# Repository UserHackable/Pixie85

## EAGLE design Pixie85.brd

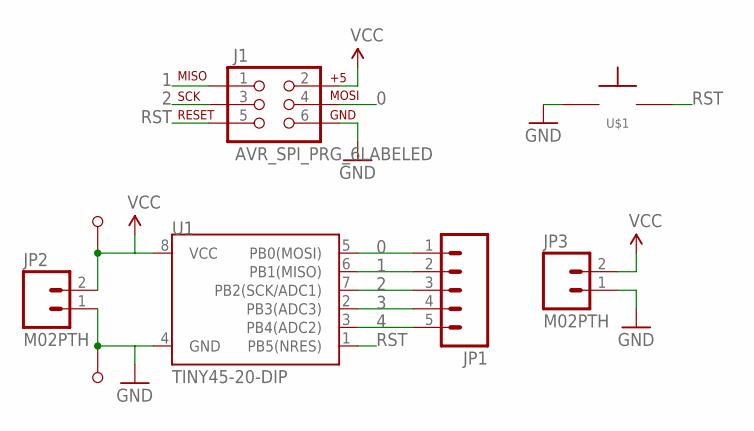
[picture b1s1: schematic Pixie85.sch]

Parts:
+: M1; M1_NO_STRAIN
-: M1; M1_NO_STRAIN
J1: AVR_SPI_PRG_6LABELED; 2X3-NS
JP1: M05PTH; 1X05
JP2, JP3: M02PTH; 1X02
U1: TINY45-20-DIP; DIP08
U$1: TAC_SPST_NO

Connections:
0: J1.4 (MOSI), JP1.1, U1.5 (PB0(MOSI))
1: J1.1 (MISO), JP1.2, U1.6 (PB1(MISO))
2: J1.3 (SCK), JP1.3, U1.7 (PB2(SCK/ADC1))
3: JP1.4, U1.2 (PB3(ADC3))
4: JP1.5, U1.3 (PB4(ADC2))
GND: -.P$1, J1.6 (GND), JP2.1, JP3.1, U1.4 (GND), U$1.P$1
RST: J1.5 (RST), U1.1 (PB5(NRES)), U$1.P$2
VCC: +.P$1, J1.2 (V+), JP2.2, JP3.2, U1.8 (VCC)

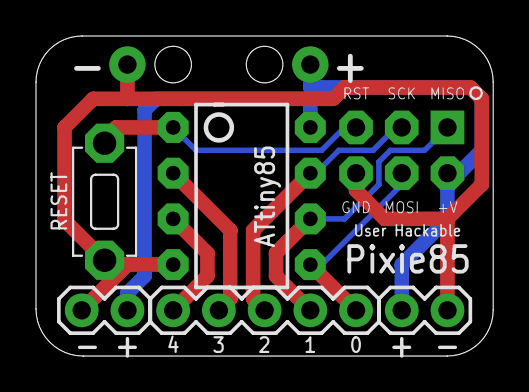
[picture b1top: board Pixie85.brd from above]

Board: 2 copper layers, 25.4 x 17.8 mm, 8 parts (0 on the bottom side), 8 nets.

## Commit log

2016-04-06 updating makefile
2016-04-07 from Makefile

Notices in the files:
parts and their libraries:
SparkFun-DigitalIC: Licensing: Creative Commons ShareAlike 4.0 International - https://creativecommons.org/licenses/by-sa/4.0
